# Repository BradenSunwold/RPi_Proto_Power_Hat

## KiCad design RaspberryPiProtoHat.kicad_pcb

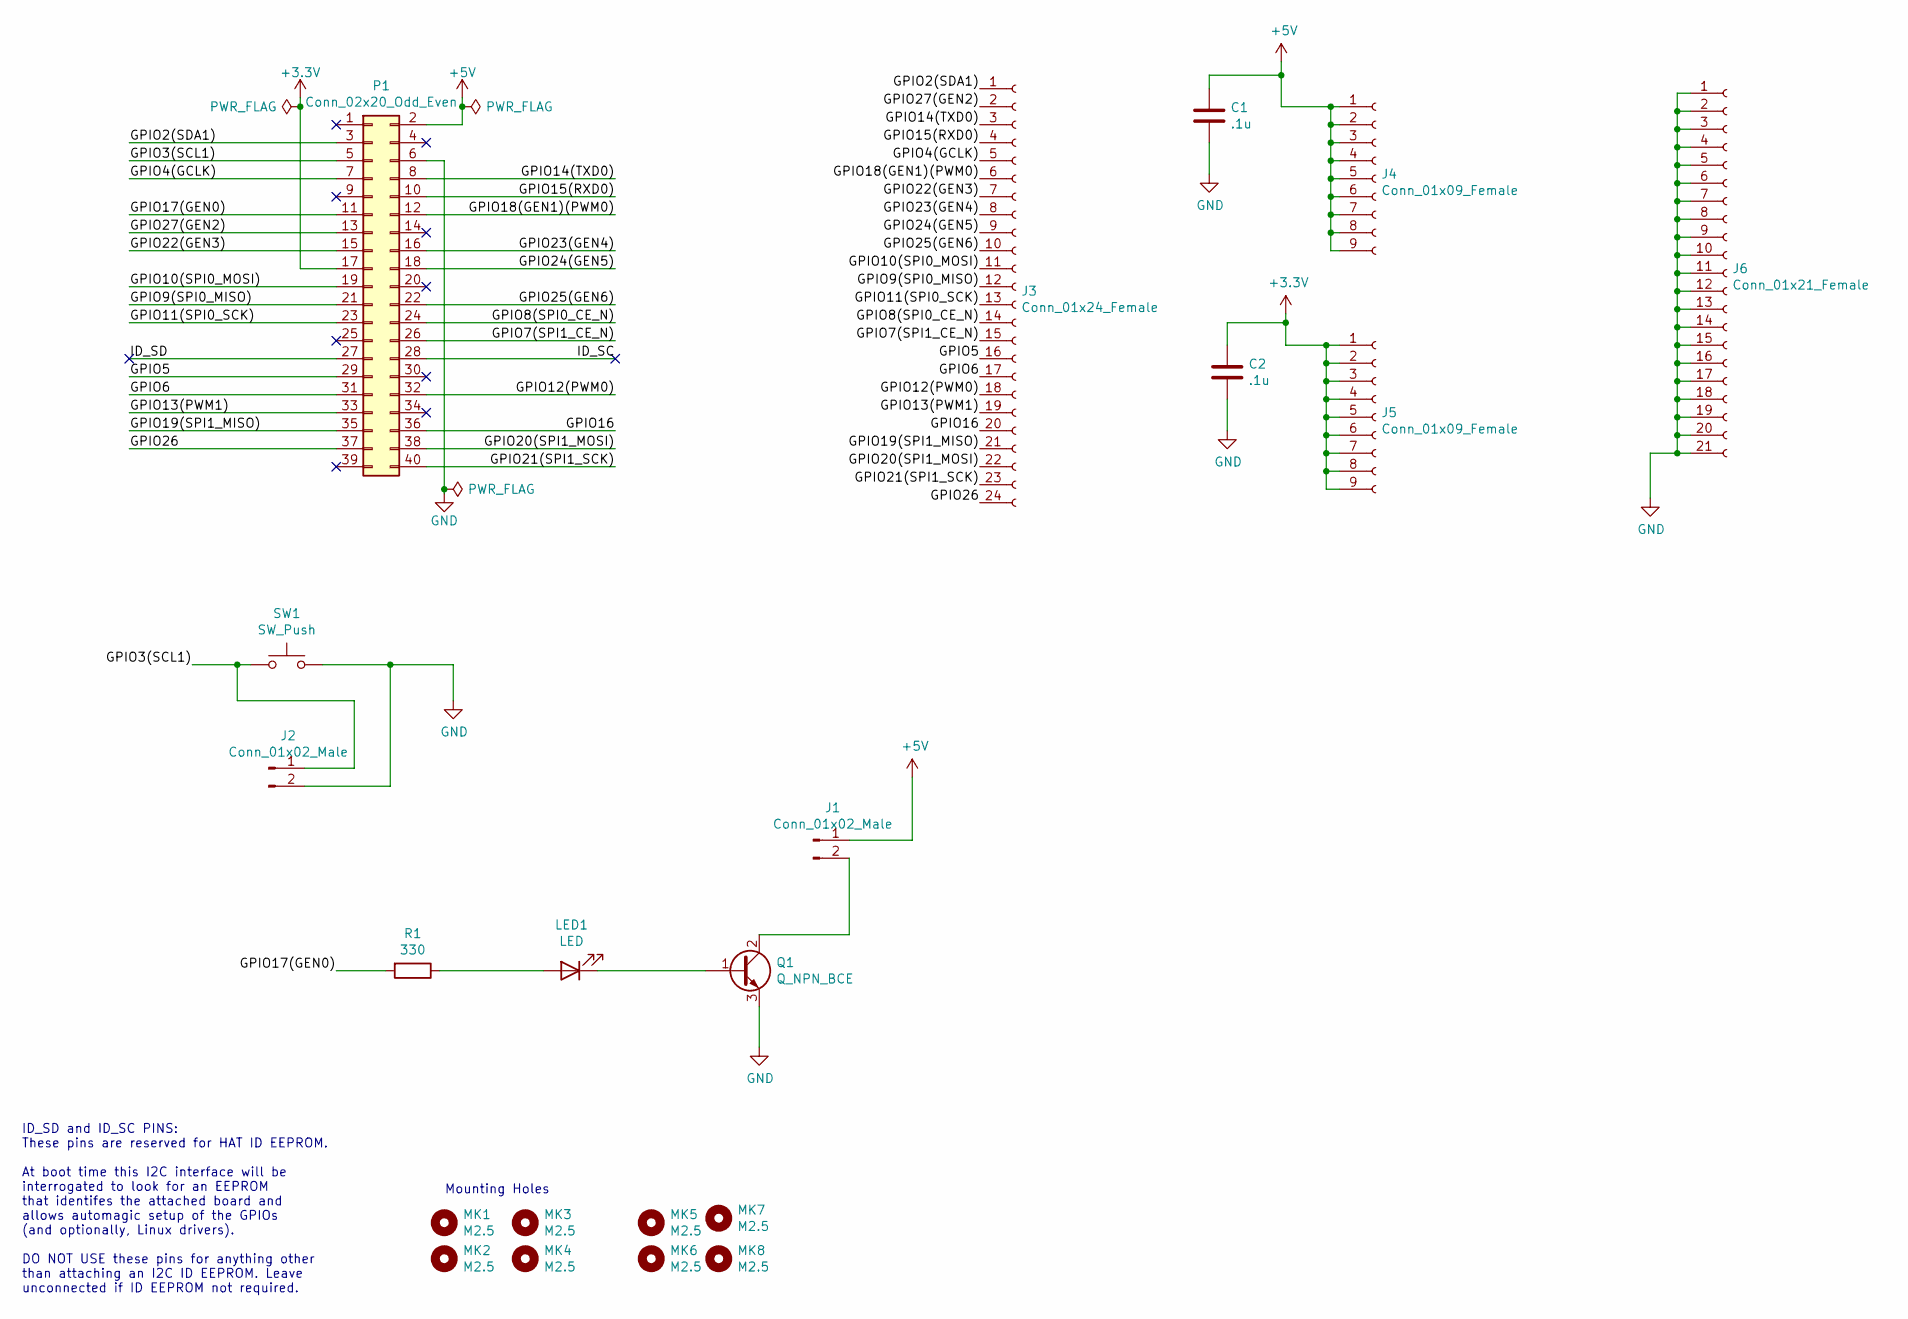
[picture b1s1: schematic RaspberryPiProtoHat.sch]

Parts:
C1, C2: .1u; C_0603_1608Metric
J1, J2: Conn_01x02_Male; PinHeader_1x02_P2.54mm_Vertical
J3: Conn_01x24_Female; PinSocket_1x24_P2.54mm_Vertical
J4, J5: Conn_01x09_Female; PinSocket_1x09_P2.54mm_Vertical
J6: Conn_01x21_Female; PinSocket_1x21_P2.54mm_Vertical
LED1: LED; LED_1206_3216Metric
MK1, MK2, MK3, MK4, MK5, MK6, MK7, MK8: M2.5; MountingHole_2.7mm_M2.5
P1: Conn_02x20_Odd_Even; PinSocket_2x20_P2.54mm_Vertical
Q1: Q_NPN_BCE; SOT-23-3
R1: 330; R_1206_3216Metric
SW1: SW_Push; SW_Push_1P1T_NO_6x6mm_H9.5mm

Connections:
+3V3: C2.1, J5.1, J5.2, J5.3, J5.4, J5.5, J5.6, J5.7, J5.8, J5.9, P1.17
+5V: C1.1, J1.1, J4.1, J4.2, J4.3, J4.4, J4.5, J4.6, J4.7, J4.8, J4.9, P1.2
/GPIO2(SDA1): J3.1, P1.3
/GPIO3(SCL1): J2.1, P1.5, SW1.1
/GPIO4(GCLK): J3.5, P1.7
/GPIO5: J3.16, P1.29
/GPIO6: J3.17, P1.31
/GPIO7(SPI1_CE_N): J3.15, P1.26
/GPIO8(SPI0_CE_N): J3.14, P1.24
/GPIO9(SPI0_MISO): J3.12, P1.21
/GPIO10(SPI0_MOSI): J3.11, P1.19
/GPIO11(SPI0_SCK): J3.13, P1.23
/GPIO12(PWM0): J3.18, P1.32
/GPIO13(PWM1): J3.19, P1.33
/GPIO14(TXD0): J3.3, P1.8
/GPIO15(RXD0): J3.4, P1.10
/GPIO16: J3.20, P1.36
/GPIO17(GEN0): P1.11, R1.2
/GPIO18(GEN1)(PWM0): J3.6, P1.12
/GPIO19(SPI1_MISO): J3.21, P1.35
/GPIO20(SPI1_MOSI): J3.22, P1.38
/GPIO21(SPI1_SCK): J3.23, P1.40
/GPIO22(GEN3): J3.7, P1.15
/GPIO23(GEN4): J3.8, P1.16
/GPIO24(GEN5): J3.9, P1.18
/GPIO25(GEN6): J3.10, P1.22
/GPIO26: J3.24, P1.37
/GPIO27(GEN2): J3.2, P1.13
/ID_SC: P1.28
/ID_SD: P1.27
GND: C1.2, C2.2, J2.2, J6.1, J6.2, J6.3, J6.4, J6.5, J6.6, J6.7, J6.8, J6.9, J6.10, J6.11, J6.12, J6.13, J6.14, J6.15, J6.16, J6.17, J6.18, J6.19, J6.20, J6.21, P1.6, Q1.3 (E), SW1.2
unnamed: J1.2, Q1.2 (C)
unnamed: LED1.1 (K), Q1.1 (B)
unnamed: LED1.2 (A), R1.1

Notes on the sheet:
ID_SD and ID_SC PINS: These pins are reserved for HAT ID EEPROM. At boot time this I2C interface will be interrogated to look for an EEPROM that identifes the attached board and allows automagic setup of the GPIOs (and optionally, Linux drivers). DO NOT USE these pins for anything other than attach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
Mounting Holes

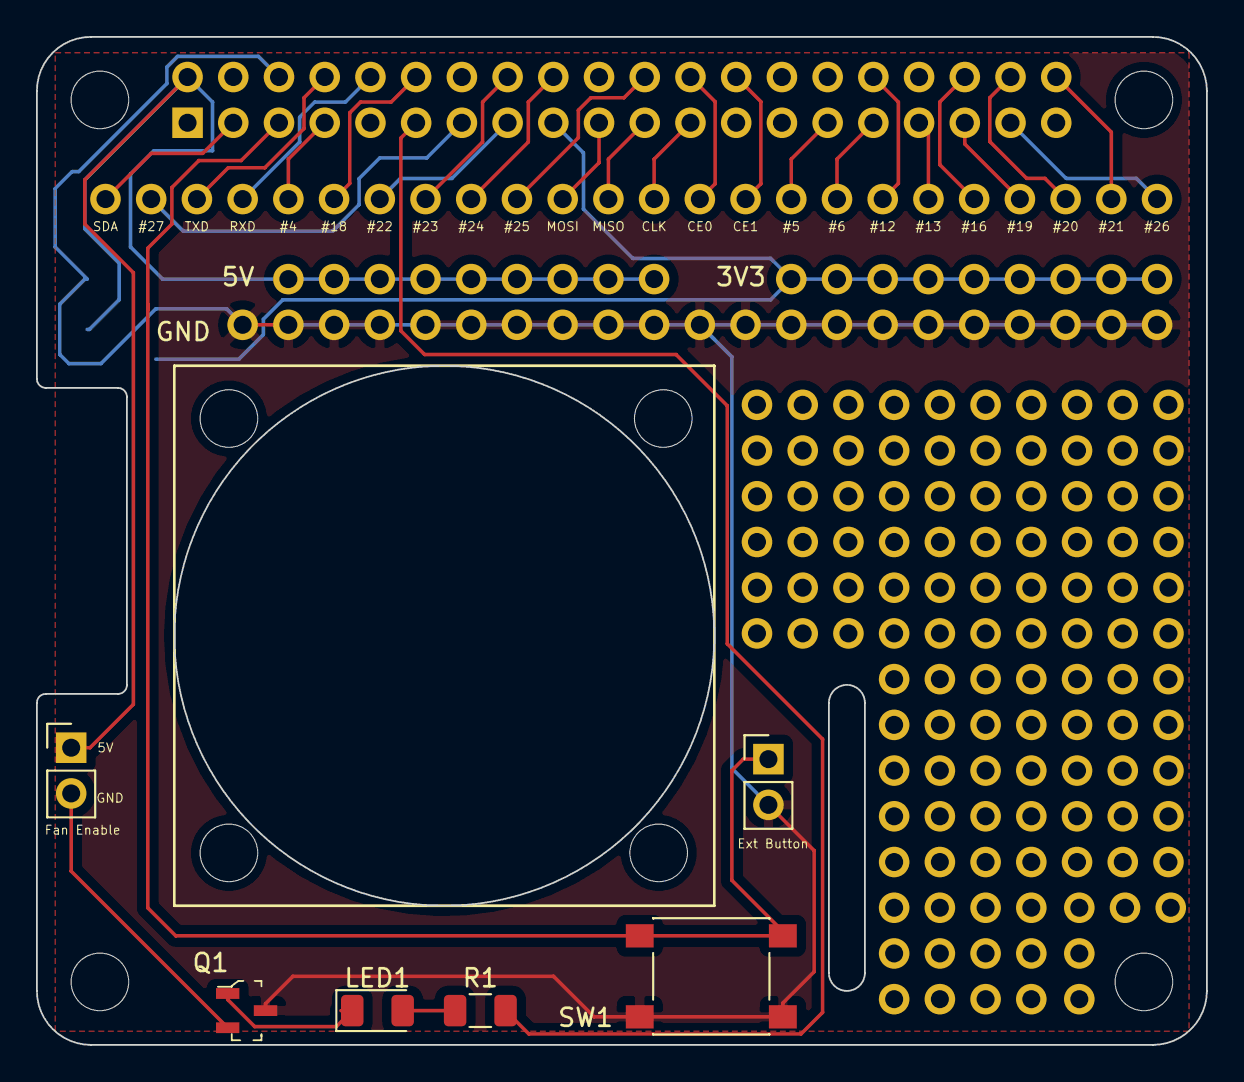
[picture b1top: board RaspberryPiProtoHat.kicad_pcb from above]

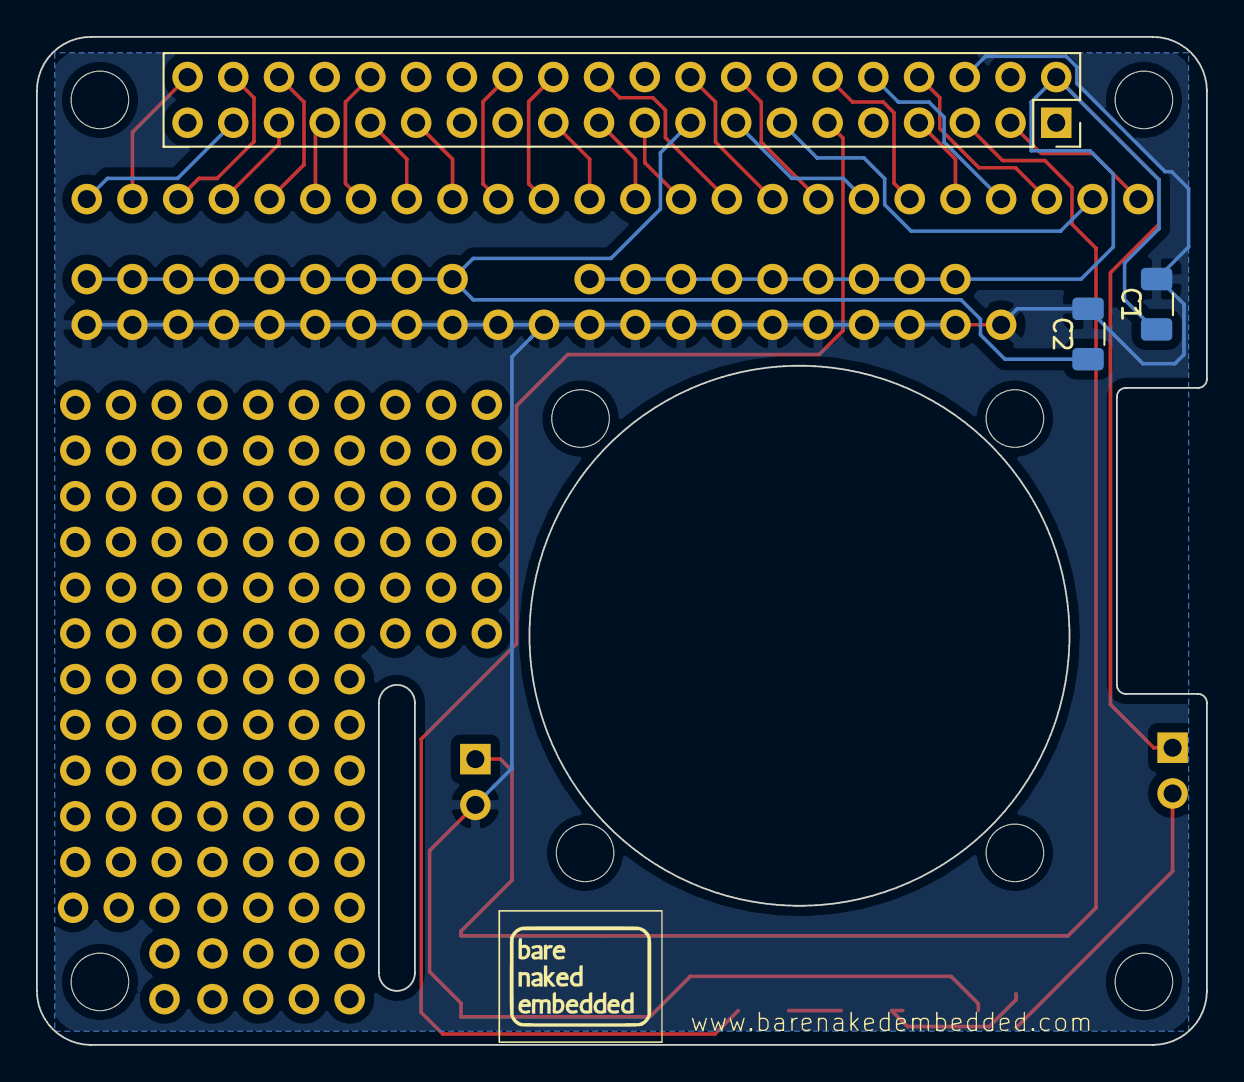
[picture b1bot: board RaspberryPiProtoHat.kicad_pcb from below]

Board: 2 copper layers, 65.0 x 56.0 mm, 21 parts (3 on the bottom side), 32 nets.

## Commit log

2023-11-04 Updated bypass capacitors to 1206 footprint for ease of soldering and added BOM
2023-11-13 Version 2.0
